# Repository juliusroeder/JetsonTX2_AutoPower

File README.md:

# JetsonTX2_AutoPower
Auto power on for the JetsonTX2 revision C02

One problem of the C02 revision of the Jetson TX2 dev kit is that auto power on is not easy to activate.
It includes desoldering and soldering 0402 resistors. The full process is described here: https://forums.developer.nvidia.com/t/auto-power-on-with-c02-carrier-board/70858

I needed a simpler way of automating the auto power on without the risk of damaging the TX2 by desoldering all other resistors next to R313.
Initially I tested the solution posted here: https://medium.com/@dumiloghin/auto-power-on-for-jetson-tx1-tx2-with-arduino-a5bd1b37659e
It turns on the TX2 using an Arduino Uno and is an excellent easy solution.

However, I needed a smaller form factor that could be co-hosted with the TX2 in a small steel enclosure.

Additionally, the only power source available to drive any logic was the 20V rail on the TX2.
In this project I am using an LDO to regulate the 20V to 5V, power an ATtiny85 microcontroller and use it to turn on the TX2 via the J20 header. The microcontroller is mostly in a sleep state and draws very little power, therefore the LDO won't heat up too much.

# Overview
The /src/ folder contains the very straigtforward main file for the ATtiny85.
The Tiny checks if the Jetson is on, if not it turns on the Jetson. If the Jetson is on then the Tiny goes into sleep mode.
The sleep mode is the deepest sleep mode available on the Tiny, but as we enable the interrupts before going to sleep the Tiny will wake up to turn on the Jetson again if it shuts down unexpectedly.

The command line commands for compiling and flashing the ATtiny85 are in the `compile.sh`.
Depending on your compiler please adjust the `-c` flag of `avrdude`.

The images folder contains additional images of the final "product".

An inital version of the PCB can be found in the PCB folder. It was created with KiCad.
Unfortunatly, I did not have the time to have it manufactured but made it by hand. Additionally, I am more of a software person than a hardware person. Please let me know if you find any boo-boo's.

# Requirements

To build your own circuit you will need the following material & equipment:

- avr-gcc, avr-objcopy, avrdude
- a bit of soldering knowledge & soldering iron
- a programmer for the ATtiny85. I use the one mentioned in the table below. If you use a different one don't forget to change it in the avrdude command. 
- the parts on the list below
- consumables (solder, jumper cables, heat shrink, some thicker (i.e. lower gauge) wire)

## List of material

Part description | Number | On Schematic | Datasheet link
-----------------|--------|--------------|---------------
ATtiny85 | 1 | U1 | http://ww1.microchip.com/downloads/en/DeviceDoc/Atmel-2586-AVR-8-bit-Microcontroller-ATtiny25-ATtiny45-ATtiny85_Datasheet.pdf
Programmer | 1 | na | e.g. https://www.fischl.de/ispnub/
LDO - L7805 TO-220 | 1 | U2 |  https://www.st.com/resource/en/datasheet/l78.pdf
BJT - 2N2222 | 1 | Q1 | https://www.onsemi.com/pub/Collateral/P2N2222A-D.PDF
Capacitor - 0.47μF | 1 | C1 | na
Capacitor - 0.22μF | 1 | C2 | na
Resistor - 200Ω | 1 | R1 | na
Resistor - at least 125Ω | 1 | R2 | na
Resistor - 1kΩ | 2 | R3 & R4 | na
LED | 1 | D1 | na

On the Schematic the BJT is a 2N2219, which should also work.

For R2 use something that matches your LED but use at least 125Ω as the Tiny I/O pins support a maximum of 40mA. I used between 500Ω to 1000Ω.

The capacitors I used are electrolytic, it would probably be better to use a ceramic cap for the 0.22μF.
On the other hand the capacitors are not essential and it should work without the caps, but keep in mind that the LDO datasheet does recommend them.

# Schematic

The connections on the board look as follows:

There are four connection points to the Jetson - H1 to H4.

* H1 goes to the *PWR* pin on the J20 header this is the pin that needs to be pulled low for 1.5 to 2 seconds to turn on the Jetson.
* H2 goes to the *OFF* pin on the J20 header and is used to detect if the Jetson is on or off.
* H3 goes to the 20V rail on the Jetson.
* H4 goes to ground on the Jetson.

More details if you are not such a hardware person (which includes me):
1. H3 goes into the LDO.
2. The LDO decreases the voltage to 5V.
3. The capacitors on the input and output of the LDO are used to decrease noise.
4. The 5 volt is used to drive the ATtiny85 via pin 8 (VCC).
5. The ATtiny85 checks if the Jetson is turned on or off - via pin 5 (PB0 going to H2).
6. If the Jetson is off the ATtiny85 sets pin 3 (PB4) to high which activates the BJT and pulls H1 low. Pulling H1 low is the same as pressing the power button.
7. The Tiny is also connected to a status LED via pin 2 (PB3). The status LED either blinks (very) slowly or is on (when the Jetson is on).
7. All ground points are connected to each other and are connected to the Jetson ground via H4.

# JetsonTX2 connections

The following image shows the top view of the TX2. The J20 header is circled in yellow.
To reach the 20V rail you need to access the bottom of the board and unscrew the 4 screws circled in red.

Solder a thicker wire to the point on the PCB circled in red. The yellow circle shows the location of the wifi antenna connectors.
The thicker wire is not essential but it will withstand a bit more physical stress.

The J20 header is shown in the next picture. The red circle shows the actual header, the yellow shows the description off the pins we actually use.
The bottom pin is the *PWR* pin, i.e. we connect this to H1.
The middle pin is the ground pin, i.e. we connect H4 here.
The top pin is the *OFF* pin, i.e. we connect H2 here.

I built my boards in such a way that I could heat shrink the three wires going to J20 together. This adds physical stability and also makes it more unlikely for individual wires to detach from the header.

# PCB
You can find the initial version of the pcb schematics, KiCad project and gerber files in the pcb folder. I have not tried to manufacture these as I ran out of time and I needed the boards asap. So I manufactured them by hand.

I changed all components to be SMD components, with the exception of the ATtiny85.

# Possible changes
- leave out the status LED - after the Jetson is turned on this consumes the most energy

# Disclaimer

I am not responsible for any damages caused to you or your equipment, board etc. When working with electronics proceed with caution. If you do not understand what you are doing, ask for the help of a professional.
That said, please do let me know if you have any suggestions!

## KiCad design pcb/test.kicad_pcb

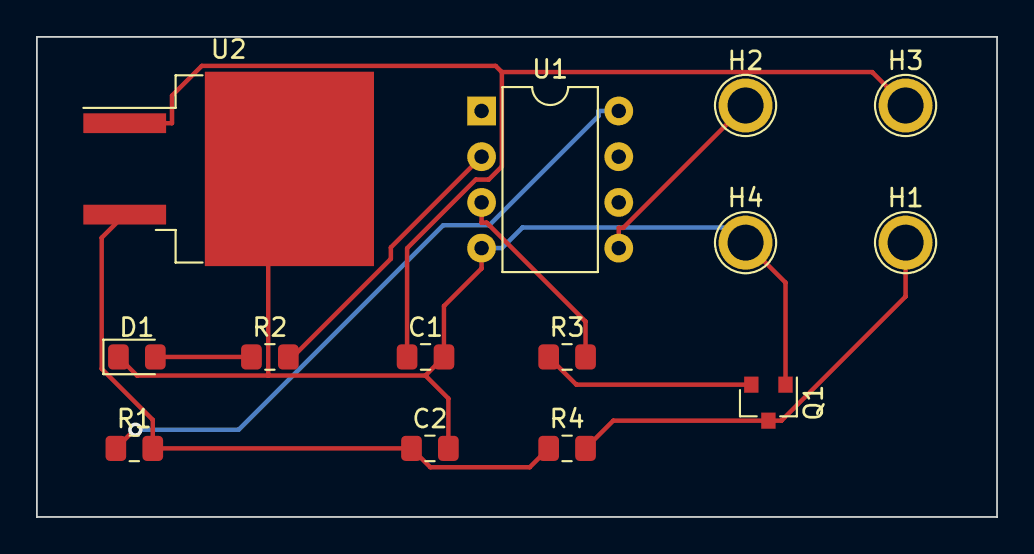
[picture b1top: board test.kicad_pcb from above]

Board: 2 copper layers, 53.3 x 26.7 mm, 14 parts (0 on the bottom side), 10 nets.

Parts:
C1: 0.47uF; C_0805_2012Metric_Pad1.15x1.40mm_HandSolder
C2: 0.22uF; C_0805_2012Metric_Pad1.15x1.40mm_HandSolder
D1: LED; LED_0805_2012Metric_Pad1.15x1.40mm_HandSolder
H1: PWR_J20; TestPoint_Plated_Hole_D2.0mm
H2: OFF_J20; TestPoint_Plated_Hole_D2.0mm
H3: VCC_Jetson; TestPoint_Plated_Hole_D2.0mm
H4: GND_Jetson; TestPoint_Plated_Hole_D2.0mm
Q1: 2N2219; SOT-23
R1: 200R; R_0805_2012Metric_Pad1.15x1.40mm_HandSolder
R2: 500R; R_0805_2012Metric_Pad1.15x1.40mm_HandSolder
R3, R4: 1k; R_0805_2012Metric_Pad1.15x1.40mm_HandSolder
U1: ATtiny85-20PU; DIP-8_W7.62mm
U2: L7805; TO-263-2

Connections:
unnamed: C1.1, H3.1, U2.1
unnamed: C1.2, C2.2, D1.1, H4.1, Q1.1, U1.4, U2.2
unnamed: C2.1, R1.2, R4.1, U2.3
unnamed: D1.2, R2.1
unnamed: H1.1, Q1.3, R4.2
unnamed: H2.1, U1.5
unnamed: Q1.2, R3.1
unnamed: R1.1, U1.8
unnamed: R2.2, U1.2
unnamed: R3.2, U1.3

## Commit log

2020-07-04 Working version of auto turn on with attiny85
2020-07-08 Small fixes and new pictures
2021-02-14 Remake of board. added programming header and moved to SMD only.
